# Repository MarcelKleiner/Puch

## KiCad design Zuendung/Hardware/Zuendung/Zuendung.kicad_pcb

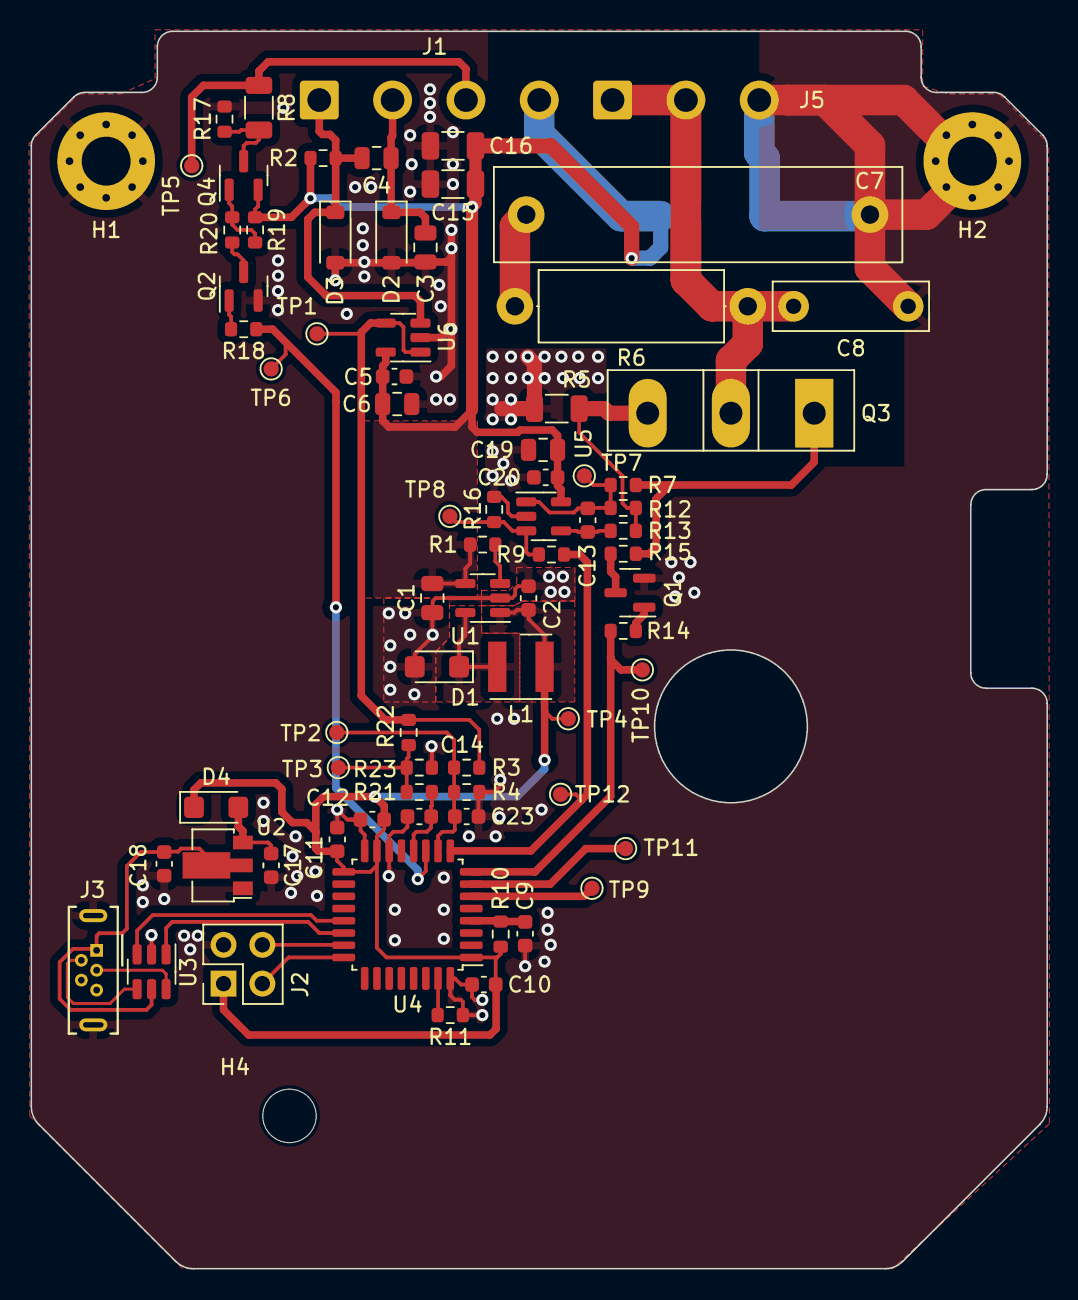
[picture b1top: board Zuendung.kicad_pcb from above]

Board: 2 copper layers, 66.5 x 81.0 mm, 79 parts (1 on the bottom side), 40 nets.

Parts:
C1, C3, C4, C6, C19: 4.7u; C_0805_2012Metric
C2: 22u; C_0603_1608Metric
C5, C9, C10, C11, C12, C20: 100n; C_0603_1608Metric
C7: 150n; C_Rect_L26.5mm_W6.0mm_P22.50mm_MKS4
C8: 10n; C_Rect_L10.0mm_W3.0mm_P7.50mm_MKS4
C13: 100p; C_0603_1608Metric
C14: 10u; C_0603_1608Metric
C15, C16: 4.7u; C_1206_3216Metric
C17: 2.2u; C_0603_1608Metric
C18: 1u; C_0603_1608Metric
C23: 10n; C_0603_1608Metric
D1, D4: 1A/60V; D_SMF
D2: DZ6V; D_SOD-123
D3: DZ12V; D_SOD-123
D5: D_Zener; D_SMC
H1, H2: MountingHole_Pad; MountingHole_3.2mm_M3_Pad_Via
H4: MountingHole; MountingHole_3.5mm
J1: Conn_01x04; SolderWire-0.75sqmm_1x04_P4.8mm_D1.25mm_OD2.3mm
J2: SWD; PinHeader_2x02_P2.54mm_Vertical
J3: USB_B_Micro; USB_Micro-B_Wuerth_614105150721_Vertical
J5: Conn_01x03; SolderWire-0.75sqmm_1x03_P4.8mm_D1.25mm_OD2.3mm
L1: 15u; L_Wurth_WE-LQSH-4020
Q1, Q2: DMN6140L; SOT-23
Q3: MSC090SMA070B; TO-247-3_Vertical
Q4: BSS83P; SOT-23
R1: 1M; R_0603_1608Metric
R2, R17, R19, R20: 10k; R_0603_1608Metric
R3, R21, R22: 6.8k; R_0603_1608Metric
R4, R23: 1.8k; R_0603_1608Metric
R5: 20m; R_1206_3216Metric
R6: 3.9; R_Axial_DIN0414_L11.9mm_D4.5mm_P15.24mm_Horizontal
R7: 750; R_0603_1608Metric
R8: 680; R_1206_3216Metric
R9: 2.4k; R_0603_1608Metric
R10, R11, R12, R13: 100k; R_0603_1608Metric
R14, R18: 120; R_0603_1608Metric
R15: 0; R_0603_1608Metric
R16: 1; R_0603_1608Metric
TP1: TachoRaw; TestPoint_Pad_D1.0mm
TP2: Tacho; TestPoint_Pad_D1.0mm
TP3: TachoMV; TestPoint_Pad_D1.0mm
TP4: 3V3; TestPoint_Pad_D1.0mm
TP5: FuelRelay; TestPoint_Pad_D1.0mm
TP6: FuelRelayFet; TestPoint_Pad_D1.0mm
TP7: ControllerOutput; TestPoint_Pad_D1.0mm
TP8: ISet; TestPoint_Pad_D1.0mm
TP9: TPDiag1; TestPoint_Pad_D1.0mm
TP10: FetOff; TestPoint_Pad_D1.0mm
TP11: TPDiag2; TestPoint_Pad_D1.0mm
TP12: ISetDAC; TestPoint_Pad_D1.0mm
U1: SOT-23-5
U2: AP2204RA-3.3; SOT-89-3
U3: USBLC6-2SC6; SOT-23-6
U4: STM32G431K8Tx; LQFP-32_7x7mm_P0.8mm
U5, U6: OPA990; SOT-23-5

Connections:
+3V3: C2.1, C10.2, C11.2, C12.2, D4.1 (K), J2.1, L1.2, R10.1, TP4.1, U1.1 (Vout), U4.1 (VDD), U4.15 (VDDA), U4.17 (VDD)
/D+: J3.3 (D+), U3.6 (I/O1)
/D-: J3.2 (D-), U3.4 (I/O2)
/SWCLK: J2.3, U4.24 (PA14)
/SWDIO: J2.4, U4.23 (PA13)
/USB_DM: U3.3 (I/O2), U4.21 (PA11)
/USB_DP: U3.1 (I/O1), U4.22 (PA12)
FETOff: R14.1, TP10.1, U4.8 (PA3)
FuelRelay: J1.3, R8.1, TP5.1
GND: C1.2, C2.2, C3.2, C5.2, C6.2, C7.1, C8.1, C9.1, C10.1, C11.1, C12.1, C14.1, C15.2, C16.2, C17.2, C18.2, C19.2, C20.2, C23.1, D1.2 (A), D2.2 (A), D3.2 (A), D5.2 (A), H1.1, H2.1, J2.2, J3.5 (GND), J3.6 (Shield), J5.3, Q1.2 (S), Q2.2 (S), R4.2, R5.2, R11.1, R16.2, R17.2, R23.2, U1.2 (GND), U2.1 (GND), U3.2 (GND), U4.14 (VSSA), U4.16 (VSS), U4.32 (VSS), U5.2 (V-), U6.2 (V-)
Ignition: C8.2, J5.1, J5.2, Q3.2 (D), R6.1
unnamed: C7.2, R6.2
unnamed: C13.1, R7.1, R12.2, TP7.1, U5.1
unnamed: D1.1 (K), L1.1, U1.5 (SW)
unnamed: C17.1, D4.2 (A), U2.3 (VOUT)
unnamed: Q1.3 (D), R15.1
unnamed: Q1.1 (G), R14.2
unnamed: Q2.3 (D), R20.2
unnamed: Q2.1 (G), R18.2
unnamed: Q3.1 (G), R7.2, R15.2
unnamed: Q3.3 (S), R5.1, R12.1, R13.1
unnamed: Q4.3 (D), R8.2, R17.1
unnamed: Q4.1 (G), R19.2, R20.1
unnamed: R1.2, U1.3 (EN)
unnamed: TP9.1, U4.6 (PA1)
unnamed: TP11.1, U4.7 (PA2)
unnamed: C14.2, R21.2, U4.12 (PA7)
unnamed: R11.2, U4.31 (PB8)
unnamed: C9.2, R10.2, U4.4 (PG10)
unnamed: R9.1, R16.1, TP8.1, U5.3 (+)
unnamed: C13.2, R13.2, U5.4 (-)
unnamed: R3.1, R22.1, TP1.1, U6.1, U6.4 (-)
RelayOutput: R18.1, TP6.1, U4.11 (PA6)
SpeedSignalMinus: C3.1, C4.1, D2.1 (K), J1.2
SpeedSignalPlus: C4.2, D3.1 (K), J1.1, R2.2, U6.3 (+)
Tacho: C23.2, R3.2, R4.1, TP2.1, U4.10 (PA5)
Tacho_MeanValue: R21.1, R22.2, R23.1, TP3.1
USet: R9.2, TP12.1, U4.9 (PA4)
VBUS: C18.1, J3.1 (VBUS), U2.2 (VIN), U3.5 (VBUS)
VCC: C1.1, C5.1, C6.1, C15.1, C16.1, C19.1, C20.1, D5.1 (K), J1.4, Q4.2 (S), R1.1, R2.1, R19.1, U1.4 (Vin), U5.5 (V+), U6.5 (V+)

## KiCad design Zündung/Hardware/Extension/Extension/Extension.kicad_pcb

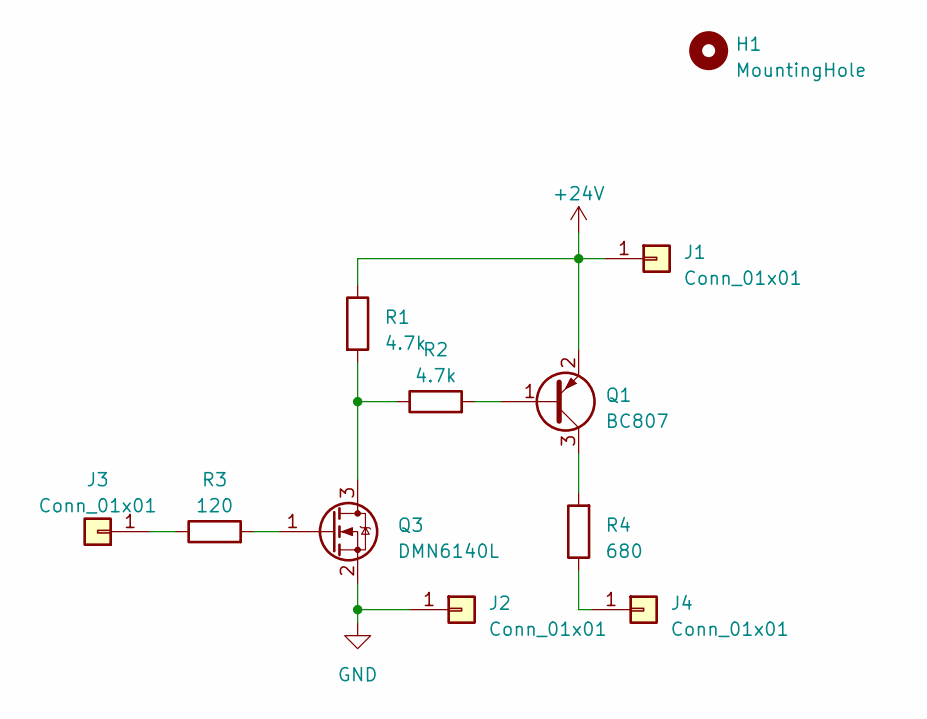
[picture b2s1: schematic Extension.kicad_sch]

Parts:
H1: MountingHole; MountingHole_3.2mm_M3
J1, J2, J3, J4: Conn_01x01; CONN_SMD
Q1: BC807; SOT-23
Q3: DMN6140L; SOT-23
R1, R2: 4.7k; R_1206_3216Metric
R3: 120; R_1206_3216Metric
R4: 680; R_1206_3216Metric

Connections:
+24V: J1.1, Q1.2 (E), R1.1
GND: J2.1, Q3.2 (S)
unnamed: J3.1, R3.1
unnamed: J4.1, R4.1
unnamed: Q1.1 (B), R2.2
unnamed: Q1.3 (C), R4.2
unnamed: Q3.3 (D), R1.2, R2.1
unnamed: Q3.1 (G), R3.2

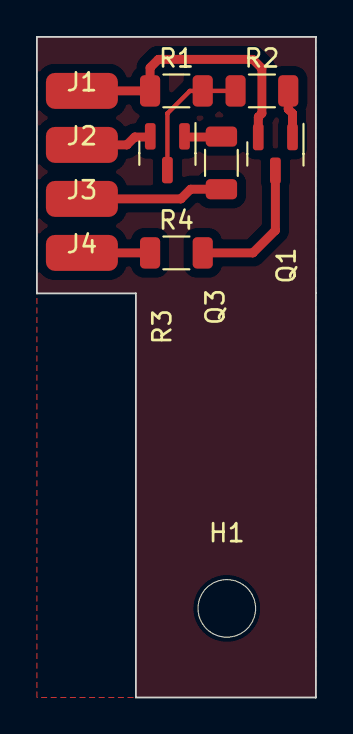
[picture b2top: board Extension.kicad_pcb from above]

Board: 2 copper layers, 15.5 x 36.7 mm, 11 parts (0 on the bottom side), 8 nets.

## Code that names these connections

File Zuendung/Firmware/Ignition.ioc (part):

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Mcu.Name=STM32G431K(6-8-B)Tx
Mcu.Package=LQFP32
Mcu.UserName=STM32G431K8Tx
PA11.Mode=Device
PA11.Signal=USB_DM
PA12.Mode=Device
PA12.Signal=USB_DP
PA13.Mode=Serial_Wire
PA13.Signal=SYS_JTMS-SWDIO
PA14.Mode=Serial_Wire
PA14.Signal=SYS_JTCK-SWCLK
PA3.GPIOParameters=GPIO_Label
PA3.GPIO_Label=IgnitionOff
PA3.Signal=GPIO_Output
PA4.GPIOParameters=GPIO_Label
PA4.GPIO_Label=ISet
PA4.Signal=COMP_DAC11_group
PA5.GPIOParameters=GPIO_Label
PA5.GPIO_Label=Tacho
PA5.Mode=IN13-Single-Ended
PA5.Signal=ADC2_IN13
PA6.GPIOParameters=GPIO_Label
PA6.GPIO_Label=Relay
PA6.Signal=GPIO_Output
PA7.GPIOParameters=GPIO_Label
PA7.GPIO_Label=TachoMeanValue
PA7.Mode=IN4-Single-Ended
PA7.Signal=ADC2_IN4
RCC.HSE_VALUE=8000000
RCC.SYSCLKFreq_VALUE=150000000
RCC.SYSCLKSource=RCC_SYSCLKSOURCE_PLLCLK
board=custom

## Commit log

2024-04-06 Update HW
2024-04-15 Hardware finalized
2024-04-15 Update folder structure
2024-04-23 Refactor project
2024-05-01 refactor software folder
2024-05-01 Change foldername
2024-05-09 update firmware and software
2024-05-09 changes for Version 2.0
2024-05-09 update Hardware
2024-05-12 udpdate Hardware
